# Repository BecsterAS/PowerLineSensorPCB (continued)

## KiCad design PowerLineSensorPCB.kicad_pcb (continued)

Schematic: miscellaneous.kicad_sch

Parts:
FID1, FID2, FID3: Fiducial; Fiducial_0.75mm_Mask1.5mm
H1, H2, H3, H4: MountingHole_Pad; MountingHole_3.2mm_M3_DIN965_Pad
J11, J12, J13: Conn_Coaxial; U.FL_Hirose_U.FL-R-SMT-1_Vertical; PartNumber BWU.FL-IPEX1; not fitted
R132, R134: 0R; R_0402_1005Metric; not fitted
R133: 50R; R_0402_1005Metric; not fitted

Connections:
GND: FID1.1, FID2.1, FID3.1, H1.1 (1_1), H2.1 (1_1), H3.1 (1_1), H4.1 (1_1), J11.2 (Ext), J12.2 (Ext), J13.2 (Ext), R132.2, R133.2, R134.2; also elsewhere on the board
unnamed: J11.1 (In), R132.1
unnamed: J12.1 (In), R133.1
unnamed: J13.1 (In), R134.1

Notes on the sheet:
Calibration connectors

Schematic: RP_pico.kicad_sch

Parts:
C3, C6, C25, C40: 4u7; C_0402_1005Metric; PartNumber CL05A475MP5NRNC
C4, C5, C9, C10, C11, C12, C13, C14, C15, C16: 100n; C_0402_1005Metric; PartNumber CL05B104KO5NNNC
C7, C8: 15p; C_0603_1608Metric; PartNumber CL10C150JB8NNNC
D2: LED; D_0603_1608Metric; PartNumber KT-0603R
J17: Conn_01x03_MountingPin; JST_SH_BM03B-SRSS-TB_1x03-1MP_P1.00mm_Vertical; PartNumber BM03B-SRSS-TB(LF)(SN)
L9: 3u3; AOTA-B201610S3R3-101-T; PartNumber AOTA-B201610S3R3-101-T
R5, R10, R33, R34, R44: 1k; R_0402_1005Metric; PartNumber 0402WGF1001TCE
R9: 33R; R_0402_1005Metric; PartNumber 0402WGF330JTCE
R11, R12, R13, R37, R38, R39, R40, R41, R46, R47: 100R; R_0402_1005Metric; PartNumber 0402WGF1000TCE
R31, R32: 22R; R_0402_1005Metric; PartNumber 0402WGF220JTCE
R87, R88, R89, R90: 100k; R_0402_1005Metric; PartNumber 0402WGF1003TCE
SW1, SW2: SW_Push; SW_SPST_EVQP2_ShortPushTravel_H2.1mm; PartNumber EVQP2T02M
U3: RP2350A; PartNumber RP2350A
U12: W25Q128JVE; W25Q; PartNumber W25Q128JVEIM; not fitted
Y1: Crystal_GND24; Crystal_SMD_3225-4Pin_3.2x2.5mm; PartNumber ABM8-272-T3

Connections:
+1V1: C6.1, L9.1, U3.6 (DVDD), U3.23 (DVDD), U3.39 (DVDD), U3.50 (VREG_FB)
+3.3V: C4.1, C5.1, C9.1, C10.1, C11.1, C12.1, C13.1, C14.1, C15.1, C16.1, C25.1, C40.1, R9.1, R33.1, R34.1, U3.1 (IOVDD), U3.11 (IOVDD), U3.20 (IOVDD), U3.30 (IOVDD), U3.38 (IOVDD), U3.44 (ADC_AVDD), U3.45 (IOVDD), U3.49 (VREG_VIN), U3.53 (USB_OTP_VDD), U3.54 (QSPI_IOVDD), U12.8 (VCC); also elsewhere on the board
/50Hz: U3.10 (GPIO7); also elsewhere on the board
/Celluar_GNSS/GNSS.RX: U3.13 (GPIO9); also elsewhere on the board
/Celluar_GNSS/GNSS.TX: R40.2; also elsewhere on the board
/Celluar_GNSS/PPS: U3.4 (GPIO2); also elsewhere on the board
/I2C0.SCL: R34.2, R47.2; also elsewhere on the board
/I2C0.SDA: R33.2, R46.2; also elsewhere on the board
/LORA/LORA.RX: U3.3 (GPIO1); also elsewhere on the board
/LORA/LORA.TX: R41.2; also elsewhere on the board
/Power/EXT_PWR.RX: U3.15 (GPIO11); also elsewhere on the board
/Power/EXT_PWR.TX: U3.14 (GPIO10); also elsewhere on the board
/Power/USB.DM: R31.1; also elsewhere on the board
/Power/USB.DP: R32.1; also elsewhere on the board
/RP_pico/A2: U3.42 (GPIO28/ADC2); also elsewhere on the board
/RP_pico/A3: U3.43 (GPIO29/ADC3); also elsewhere on the board
/RP_pico/QSPI_SCLK: U3.56 (QSPI_SCLK), U12.6 (CLK)
/RP_pico/QSPI_SD0: U3.57 (QSPI_SD0), U12.5 (DI/IO_{0})
/RP_pico/QSPI_SD1: U3.59 (QSPI_SD1), U12.2 (DO/IO_{1})
/RP_pico/QSPI_SD2: U3.58 (QSPI_SD2), U12.3 (~WP/IO_{2})
/RP_pico/QSPI_SD3: U3.55 (QSPI_SD3), U12.7 (~HOLD/~RESET/IO_{3})
/RP_pico/QSPI_SS: R5.2, U3.60 (~QSPI_SS), U12.1 (~CS)
/RP_pico/RUN: SW2.1, U3.26 (RUN)
/RP_pico/SC: R11.1, U3.24 (SWCLK)
/RP_pico/SD: R12.1, U3.25 (SWDIO)
/RP_pico/SPI0.RX: U3.27 (GPIO16); also elsewhere on the board
/RP_pico/SPI0.SCK: R37.2; also elsewhere on the board
/RP_pico/SPI0.TX: R39.2; also elsewhere on the board
/RP_pico/U1: R87.1, U3.37 (GPIO25)
/RP_pico/U2: R88.1, U3.17 (GPIO13)
/RP_pico/U3: R89.1, U3.34 (GPIO22)
/RP_pico/U4: R90.1, U3.9 (GPIO6)
/RP_pico/XIN: C7.1, U3.21 (XIN), Y1.1
/RP_pico/XOUT: R10.1, U3.22 (XOUT)
/RP_pico/XR: C8.1, R10.2, Y1.3
/hall effect sensor/Out: U3.41 (GPIO27/ADC1); also elsewhere on the board
/sens1: U3.40 (GPIO26/ADC0); also elsewhere on the board
GND: C3.2, C4.2, C5.2, C6.2, C7.2, C8.2, C9.2, C10.2, C11.2, C12.2, C13.2, C14.2, C15.2, C16.2, C25.2, C40.2, D2.1 (K), J17.2, J17.MP (MountPin), R44.1, R87.2, R88.2, R89.2, R90.2, SW1.1, U3.47 (VREG_PGND), U3.61 (GND), U12.4 (GND), U12.9 (EP), Y1.2 (G), Y1.4 (G); also elsewhere on the board
GNSS_~RESET: U3.33 (GPIO21); also elsewhere on the board
LORA_~RST: U3.32 (GPIO20); also elsewhere on the board
unnamed: D2.2 (A), R13.2
unnamed: J17.1, R11.2
unnamed: J17.3, R12.2
unnamed: R5.1, SW1.2
unnamed: R44.2, SW2.2
unnamed: R41.1, U3.2 (GPIO0)
unnamed: R46.1, U3.7 (GPIO4)
unnamed: R47.1, U3.8 (GPIO5)
unnamed: R40.1, U3.12 (GPIO8)
unnamed: R13.1, U3.16 (GPIO12)
unnamed: R38.1, U3.28 (GPIO17)
unnamed: R37.1, U3.29 (GPIO18)
unnamed: R39.1, U3.31 (GPIO19)
unnamed: R31.2, U3.51 (USB_DM)
unnamed: R32.2, U3.52 (USB_DP)
unnamed: C3.1, R9.2, U3.46 (VREG_AVDD)
unnamed: L9.2, U3.48 (VREG_LX)
Power_ext: U3.35 (GPIO23); also elsewhere on the board
Power_usb: U3.36 (GPIO24); also elsewhere on the board
Pulse_Switch_converter: U3.5 (GPIO3); also elsewhere on the board
~CS_Accelerometer: U3.19 (GPIO15); also elsewhere on the board
~CS_SDCard: R38.2; also elsewhere on the board
~INT_Battery_Charger: U3.18 (GPIO14); also elsewhere on the board

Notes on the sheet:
IOVDD caps
Max 400 pF bus capacitance
1v1 Regulator components.

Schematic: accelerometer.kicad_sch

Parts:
C22, C23: 100n; C_0402_1005Metric; PartNumber CL05B104KO5NNNC
C24: 4u7; C_0402_1005Metric; PartNumber CL05A475MP5NRNC
R42: 100R; R_0402_1005Metric; PartNumber 0402WGF1000TCE
U7: LIS2HH12; LGA-12_2x2mm_P0.5mm; PartNumber LIS2HH12

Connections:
+3.3V: C22.1, C23.1, C24.1, U7.9 (Vdd), U7.10 (Vdd_IO); also elsewhere on the board
/RP_pico/SPI0.RX: R42.1; also elsewhere on the board
/RP_pico/SPI0.SCK: U7.1 (SCL/SPC); also elsewhere on the board
/RP_pico/SPI0.TX: U7.4 (SDA/SDI); also elsewhere on the board
GND: C22.2, C23.2, C24.2, U7.5 (RES), U7.6 (GND), U7.7 (GND), U7.8 (GND); also elsewhere on the board
unnamed: R42.2, U7.3 (SA0/SDO)
~CS_Accelerometer: U7.2 (~CS); also elsewhere on the board

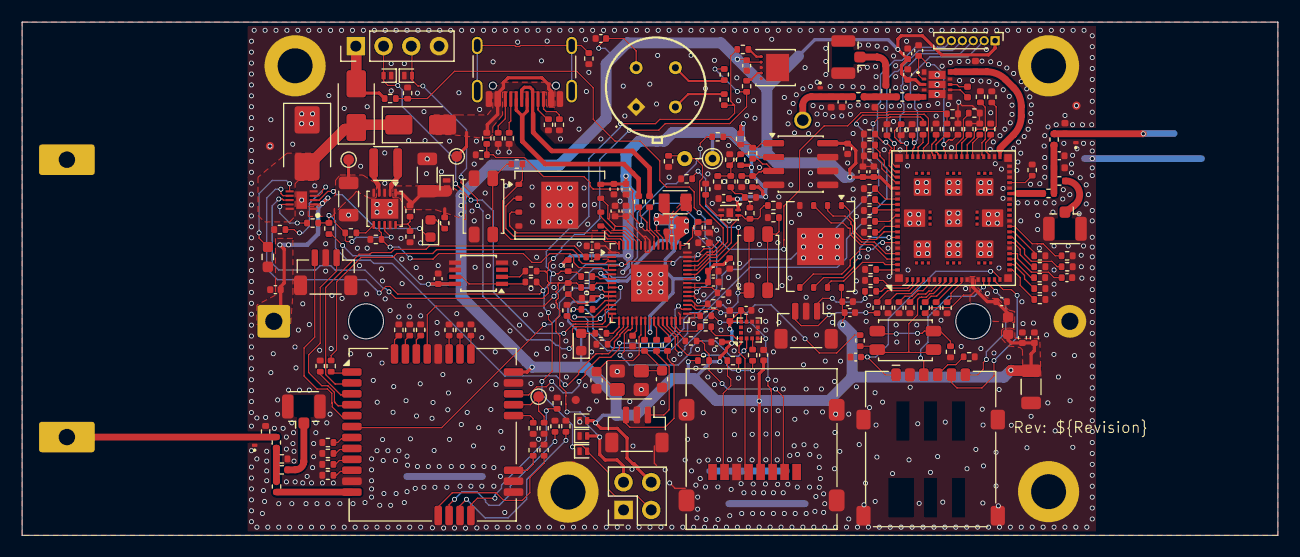
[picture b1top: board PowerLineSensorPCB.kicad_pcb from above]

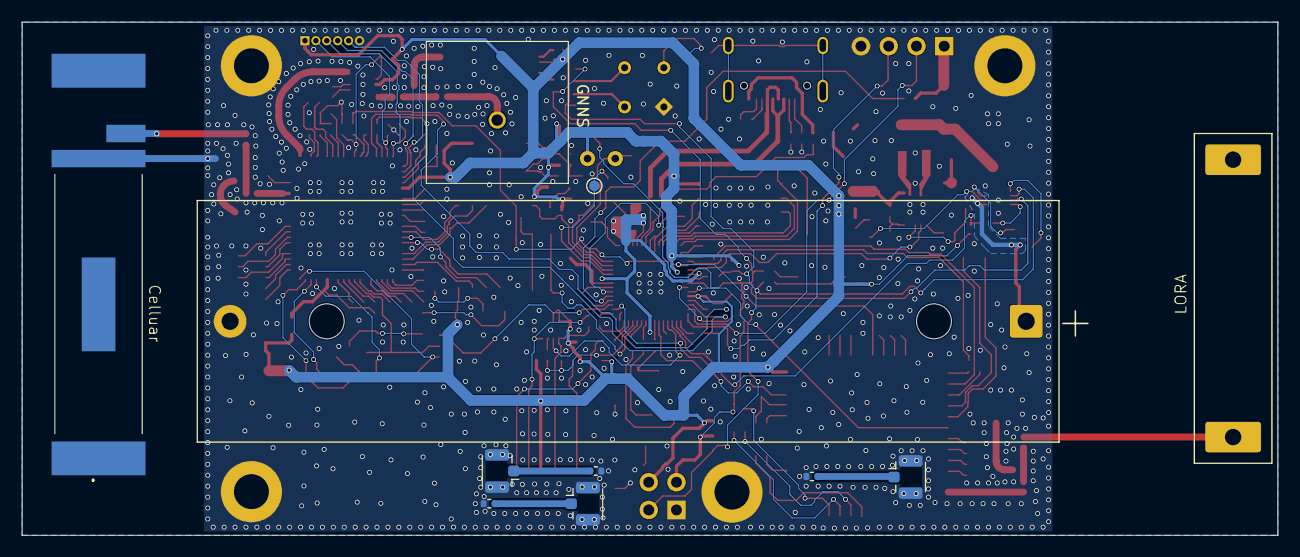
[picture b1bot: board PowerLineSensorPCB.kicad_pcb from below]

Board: 4 copper layers, 115.0 x 47.0 mm, 255 parts (11 on the bottom side), 189 nets.

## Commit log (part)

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2026-06-29 initial PCB
2026-06-29 update kicadlib
